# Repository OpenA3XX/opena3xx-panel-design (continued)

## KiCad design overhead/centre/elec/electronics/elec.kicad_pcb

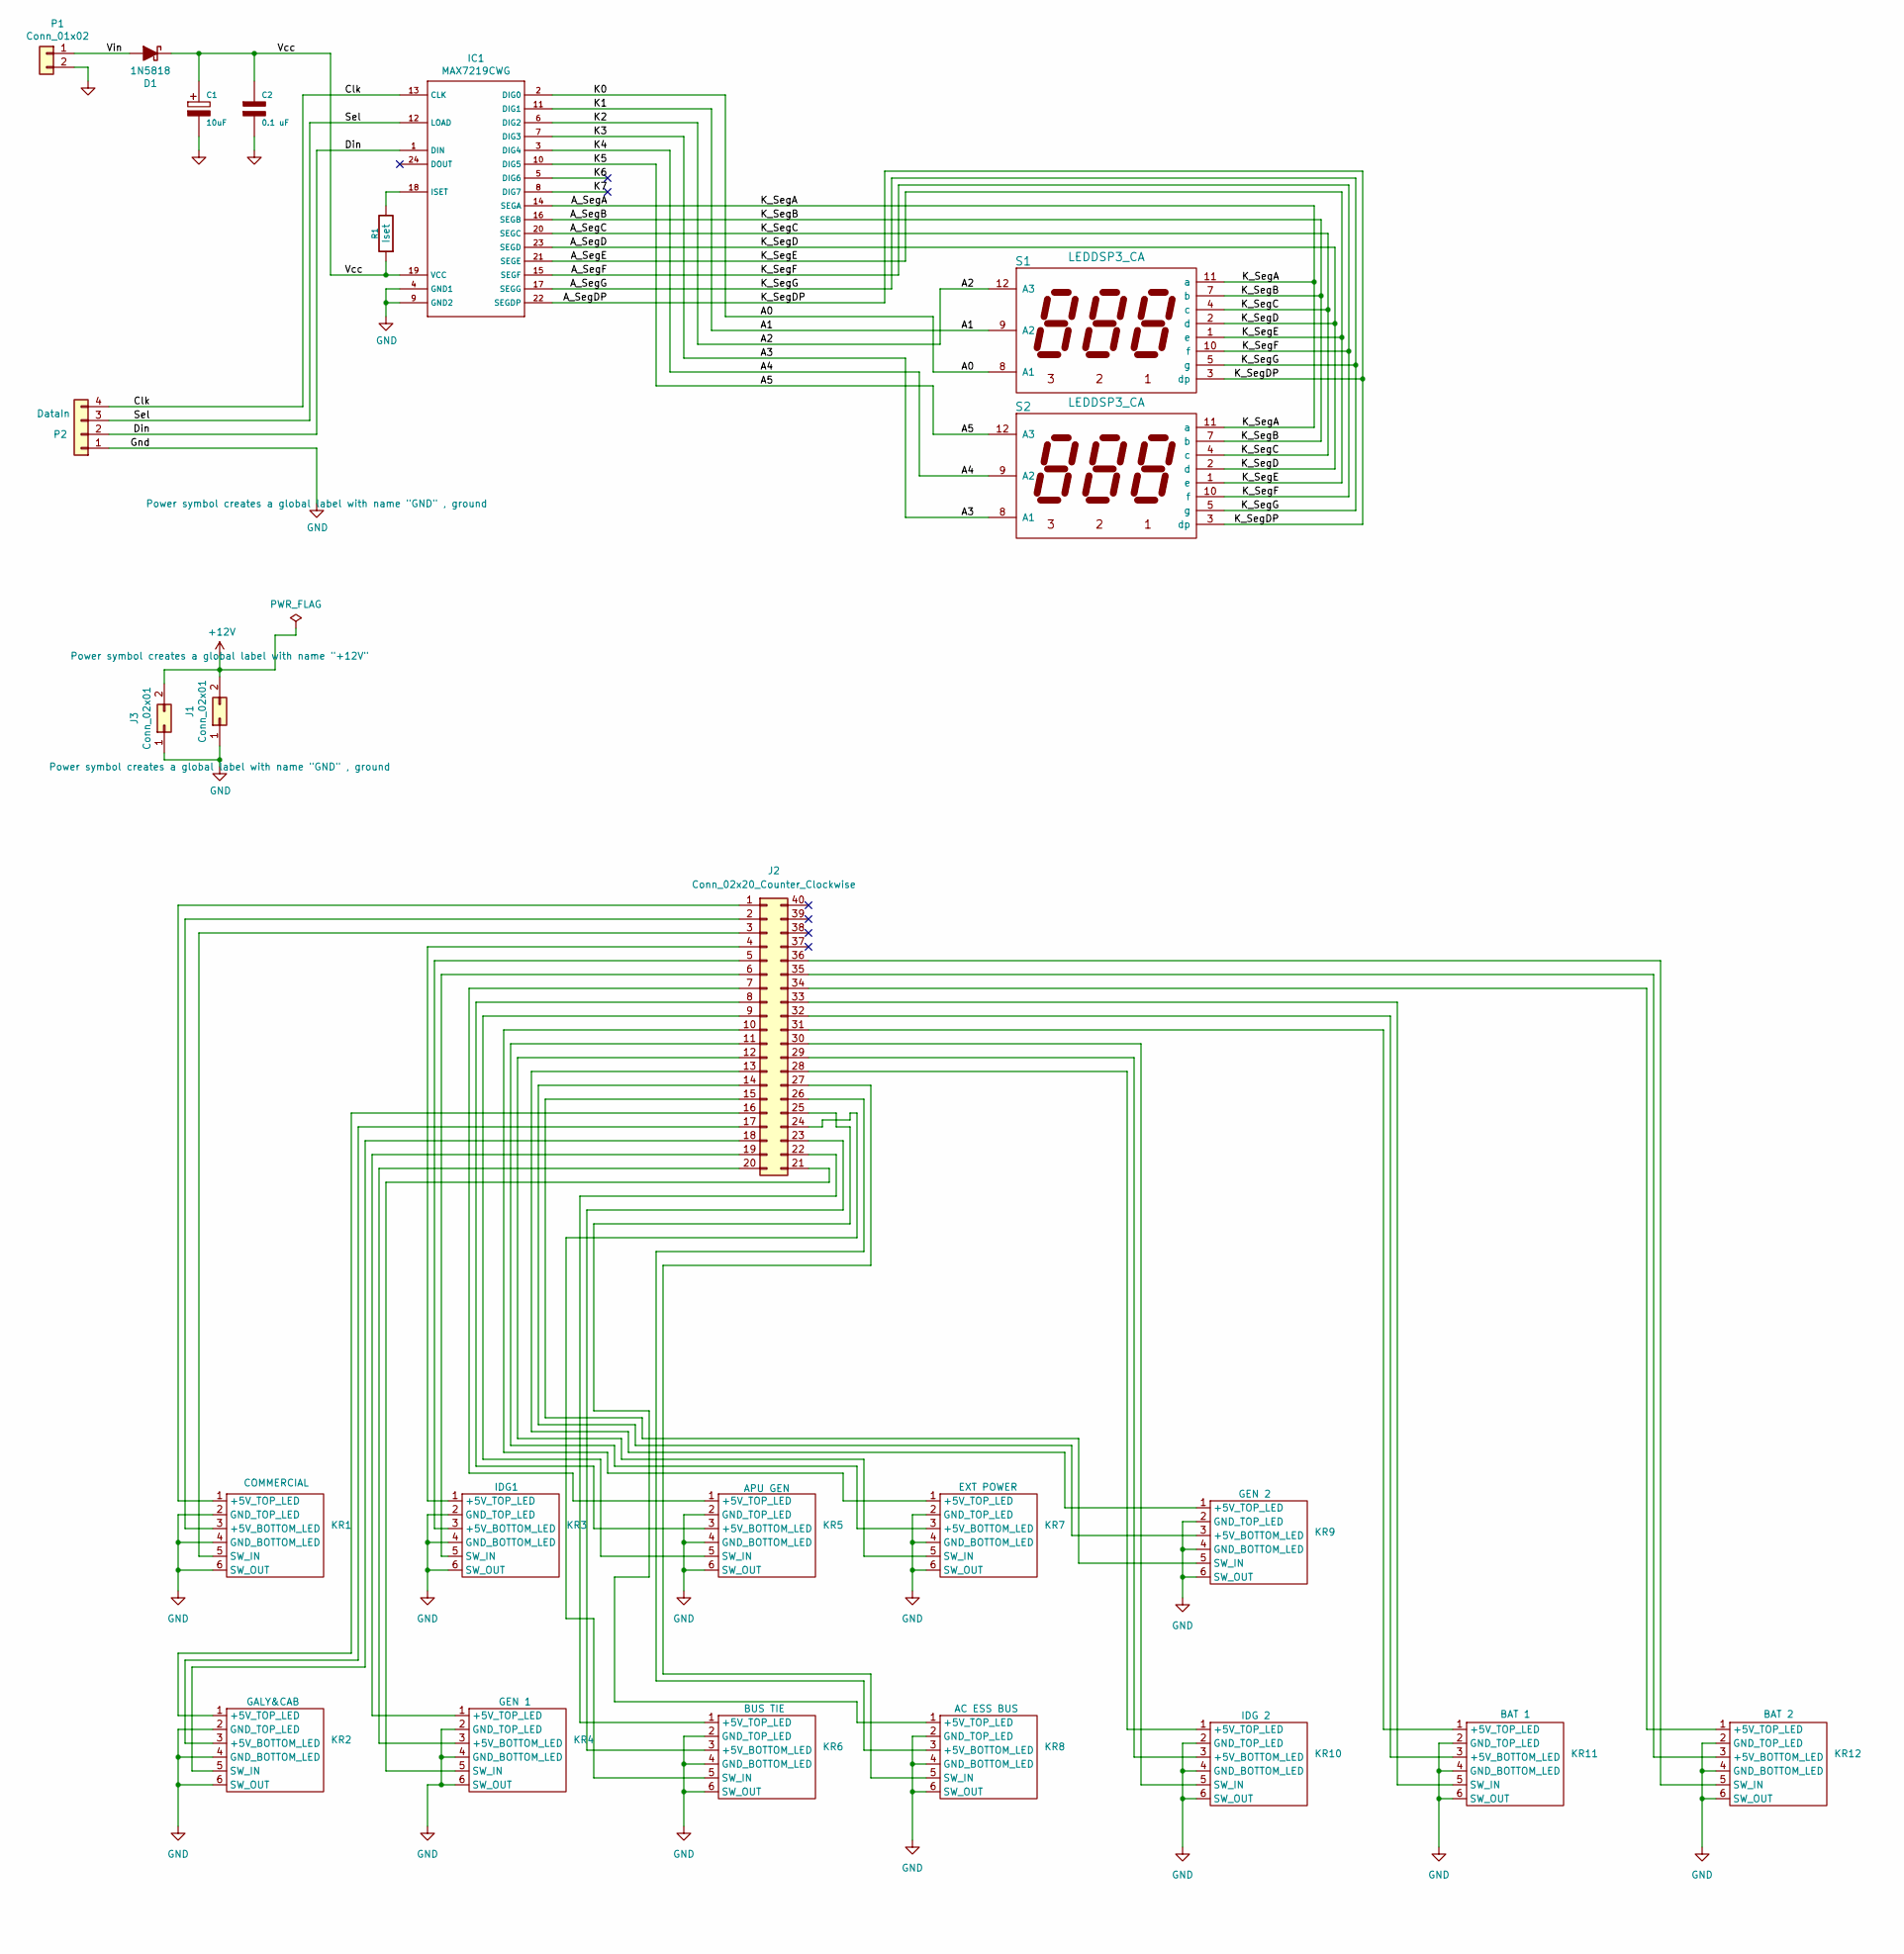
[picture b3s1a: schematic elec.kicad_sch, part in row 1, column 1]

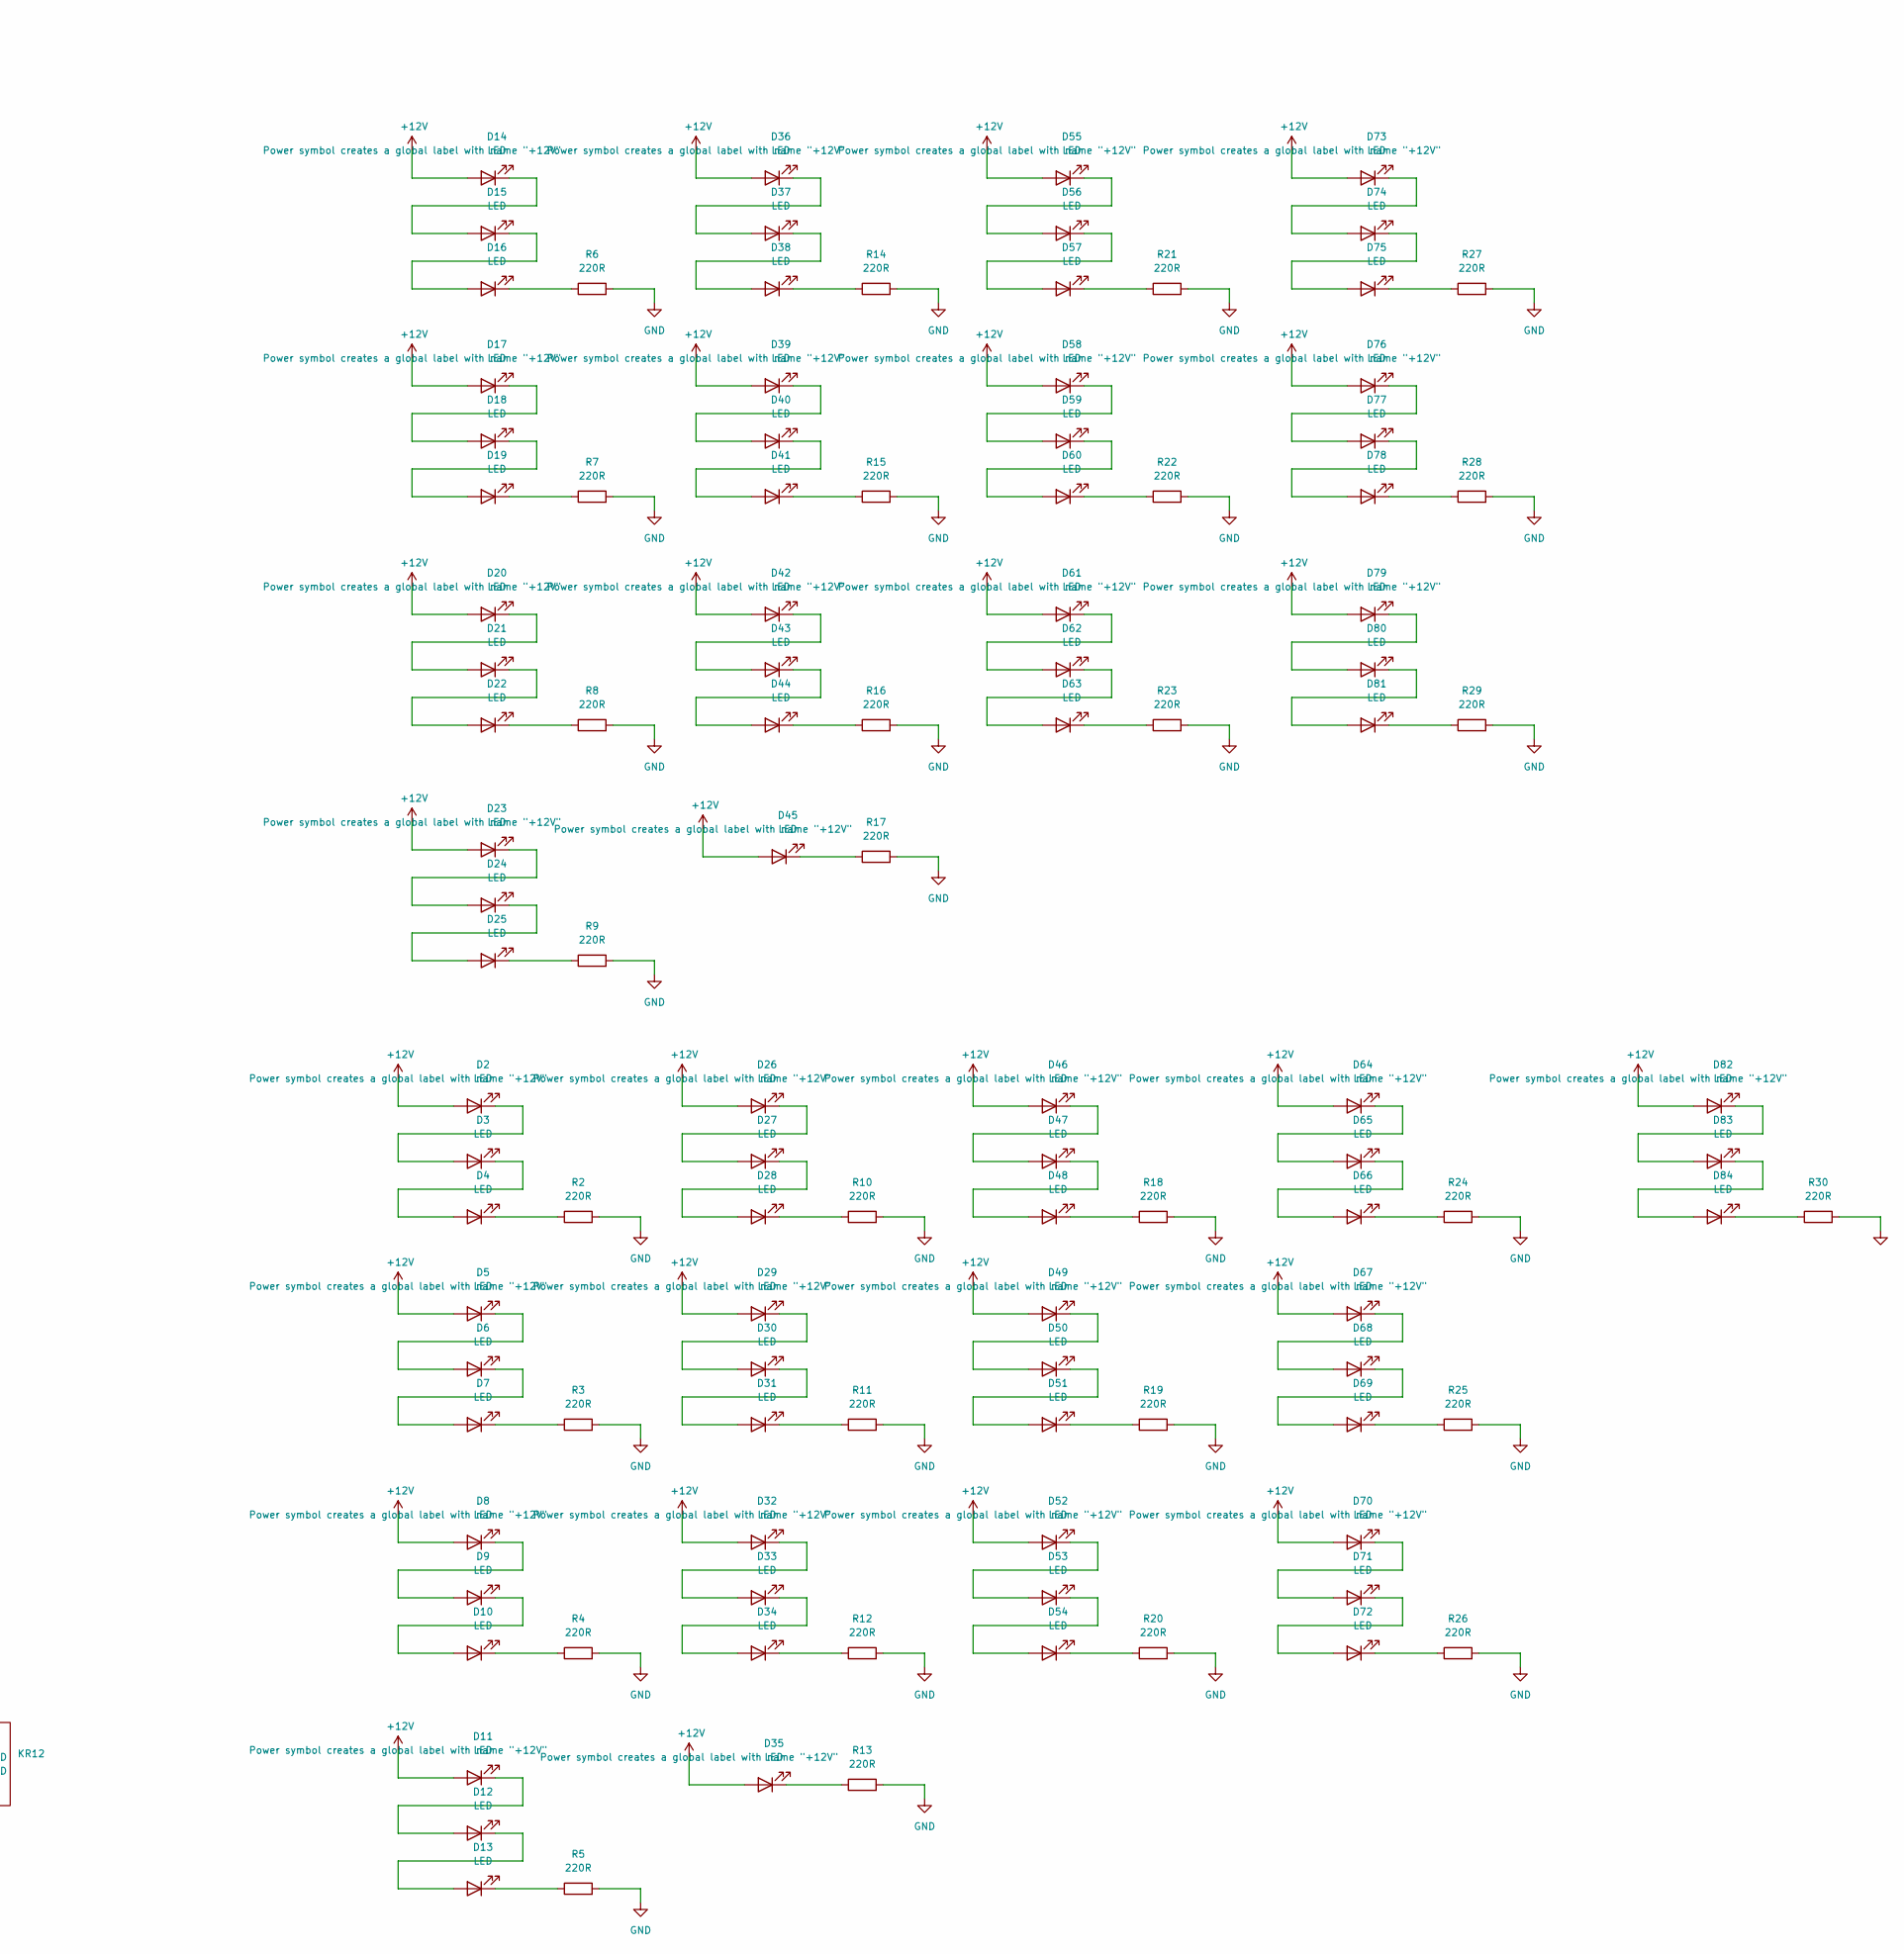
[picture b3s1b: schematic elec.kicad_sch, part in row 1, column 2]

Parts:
C1: 10uF; CP_Radial_D5.0mm_P2.50mm
C2: 0.1 uF; C_1206_3216Metric_Pad1.33x1.80mm_HandSolder
D1: 1N5818; D_SMA_Handsoldering
D2, D3, D4, D5, D6, D7, D8, D9, D10, D11, D12, D13, D14, D15, D16, D17, D18, D19, D20, D21, D22, D23, D24, D25, D26, D27, D28, D29, D30, D31, D32, D33, D34, D35, D36, D37, D38, D39, D40, D41, D42, D43, D44, D45, D46, D47, D48, D49, D50, D51, D52, D53, D54, D55, D56, D57, D58, D59, D60, D61, D62, D63, D64, D65, D66, D67, D68, D69, D70, D71, D72, D73, D74, D75, D76, D77, D78, D79, D80, D81, D82, D83, D84: LED; LED_Everlight-SMD3528_3.5x2.8mm_67-21ST
IC1: MAX7219CWG; SOIC-24W_7.5x15.4mm_P1.27mm
J1, J3: Conn_02x01; TerminalBlock_bornier-2_P5.08mm
J2: Conn_02x20_Counter_Clockwise; PinHeader_2x20_P2.54mm_Vertical
KR1, KR2, KR3, KR4, KR5, KR6, KR7, KR8, KR9, KR10, KR11, KR12: Korry Switch
P1: Conn_01x02; TerminalBlock_bornier-2_P5.08mm
P2: DataIn; PinHeader_1x04_P2.54mm_Vertical
R1: Iset; R_Axial_DIN0207_L6.3mm_D2.5mm_P10.16mm_Horizontal
R2, R3, R4, R5, R6, R7, R8, R9, R10, R11, R12, R13, R14, R15, R16, R17, R18, R19, R20, R21, R22, R23, R24, R25, R26, R27, R28, R29, R30: 220R; R_1206_3216Metric_Pad1.30x1.75mm_HandSolder
S1, S2: LEDDSP3_CA; Disp7s3x_036

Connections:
+12V: D2.2 (A), D5.2 (A), D8.2 (A), D11.2 (A), D14.2 (A), D17.2 (A), D20.2 (A), D23.2 (A), D26.2 (A), D29.2 (A), D32.2 (A), D35.2 (A), D36.2 (A), D39.2 (A), D42.2 (A), D45.2 (A), D46.2 (A), D49.2 (A), D52.2 (A), D55.2 (A), D58.2 (A), D61.2 (A), D64.2 (A), D67.2 (A), D70.2 (A), D73.2 (A), D76.2 (A), D79.2 (A), D82.2 (A), J1.2, J3.2
/A0: IC1.2 (DIG0), S1.8 (A1)
/A1: IC1.11 (DIG1), S1.9 (A2)
/A2: IC1.6 (DIG2), S1.12 (A3)
/A3: IC1.7 (DIG3), S2.8 (A1)
/A4: IC1.3 (DIG4), S2.9 (A2)
/A5: IC1.10 (DIG5), S2.12 (A3)
/A_SegA: IC1.14 (SEGA), S1.11 (a), S2.11 (a)
/A_SegB: IC1.16 (SEGB), S1.7 (b), S2.7 (b)
/A_SegC: IC1.20 (SEGC), S1.4 (c), S2.4 (c)
/A_SegD: IC1.23 (SEGD), S1.2 (d), S2.2 (d)
/A_SegDP: IC1.22 (SEGDP), S1.3 (dp), S2.3 (dp)
/A_SegE: IC1.21 (SEGE), S1.1 (e), S2.1 (e)
/A_SegF: IC1.15 (SEGF), S1.10 (f), S2.10 (f)
/A_SegG: IC1.17 (SEGG), S1.5 (g), S2.5 (g)
/Clk: IC1.13 (CLK), P2.4
/Din: IC1.1 (DIN), P2.2
/K6: IC1.5 (DIG6)
/K7: IC1.8 (DIG7)
/Sel: IC1.12 (LOAD), P2.3
/Vcc: C1.1, C2.1, D1.1 (K), IC1.19 (VCC), R1.1
/Vin: D1.2 (A), P1.1
GND: C1.2, C2.2, IC1.4 (GND1), IC1.9 (GND2), J1.1, J3.1, KR1.2 (GND_TOP_LED), KR1.4 (GND_BOTTOM_LED), KR1.6 (SW_OUT), KR2.2 (GND_TOP_LED), KR2.4 (GND_BOTTOM_LED), KR2.6 (SW_OUT), KR3.2 (GND_TOP_LED), KR3.4 (GND_BOTTOM_LED), KR3.6 (SW_OUT), KR4.2 (GND_TOP_LED), KR4.4 (GND_BOTTOM_LED), KR4.6 (SW_OUT), KR5.2 (GND_TOP_LED), KR5.4 (GND_BOTTOM_LED), KR5.6 (SW_OUT), KR6.2 (GND_TOP_LED), KR6.4 (GND_BOTTOM_LED), KR6.6 (SW_OUT), KR7.2 (GND_TOP_LED), KR7.4 (GND_BOTTOM_LED), KR7.6 (SW_OUT), KR8.2 (GND_TOP_LED), KR8.4 (GND_BOTTOM_LED), KR8.6 (SW_OUT), KR9.2 (GND_TOP_LED), KR9.4 (GND_BOTTOM_LED), KR9.6 (SW_OUT), KR10.2 (GND_TOP_LED), KR10.4 (GND_BOTTOM_LED), KR10.6 (SW_OUT), KR11.2 (GND_TOP_LED), KR11.4 (GND_BOTTOM_LED), KR11.6 (SW_OUT), KR12.2 (GND_TOP_LED), KR12.4 (GND_BOTTOM_LED), KR12.6 (SW_OUT), P1.2, P2.1, R2.2, R3.2, R4.2, R5.2, R6.2, R7.2, R8.2, R9.2, R10.2, R11.2, R12.2, R13.2, R14.2, R15.2, R16.2, R17.2, R18.2, R19.2, R20.2, R21.2, R22.2, R23.2, R24.2, R25.2, R26.2, R27.2, R28.2, R29.2, R30.2
unnamed: D2.1 (K), D3.2 (A)
unnamed: D3.1 (K), D4.2 (A)
unnamed: D4.1 (K), R2.1
unnamed: D5.1 (K), D6.2 (A)
unnamed: D6.1 (K), D7.2 (A)
unnamed: D7.1 (K), R3.1
unnamed: D8.1 (K), D9.2 (A)
unnamed: D9.1 (K), D10.2 (A)
unnamed: D10.1 (K), R4.1
unnamed: D11.1 (K), D12.2 (A)
unnamed: D12.1 (K), D13.2 (A)
unnamed: D13.1 (K), R5.1
unnamed: D14.1 (K), D15.2 (A)
unnamed: D15.1 (K), D16.2 (A)
unnamed: D16.1 (K), R6.1
unnamed: D17.1 (K), D18.2 (A)
unnamed: D18.1 (K), D19.2 (A)
unnamed: D19.1 (K), R7.1
unnamed: D20.1 (K), D21.2 (A)
unnamed: D21.1 (K), D22.2 (A)
unnamed: D22.1 (K), R8.1
unnamed: D23.1 (K), D24.2 (A)
unnamed: D24.1 (K), D25.2 (A)
unnamed: D25.1 (K), R9.1
unnamed: D26.1 (K), D27.2 (A)
unnamed: D27.1 (K), D28.2 (A)
unnamed: D28.1 (K), R10.1
unnamed: D29.1 (K), D30.2 (A)
unnamed: D30.1 (K), D31.2 (A)
unnamed: D31.1 (K), R11.1
unnamed: D32.1 (K), D33.2 (A)
unnamed: D33.1 (K), D34.2 (A)
unnamed: D34.1 (K), R12.1
unnamed: D35.1 (K), R13.1
unnamed: D36.1 (K), D37.2 (A)
unnamed: D37.1 (K), D38.2 (A)
unnamed: D38.1 (K), R14.1
unnamed: D39.1 (K), D40.2 (A)
unnamed: D40.1 (K), D41.2 (A)
unnamed: D41.1 (K), R15.1
unnamed: D42.1 (K), D43.2 (A)
unnamed: D43.1 (K), D44.2 (A)
unnamed: D44.1 (K), R16.1
unnamed: D45.1 (K), R17.1
unnamed: D46.1 (K), D47.2 (A)
unnamed: D47.1 (K), D48.2 (A)
unnamed: D48.1 (K), R18.1
unnamed: D49.1 (K), D50.2 (A)
unnamed: D50.1 (K), D51.2 (A)
unnamed: D51.1 (K), R19.1
unnamed: D52.1 (K), D53.2 (A)
unnamed: D53.1 (K), D54.2 (A)
unnamed: D54.1 (K), R20.1
unnamed: D55.1 (K), D56.2 (A)
unnamed: D56.1 (K), D57.2 (A)
unnamed: D57.1 (K), R21.1
unnamed: D58.1 (K), D59.2 (A)
unnamed: D59.1 (K), D60.2 (A)
unnamed: D60.1 (K), R22.1
unnamed: D61.1 (K), D62.2 (A)
unnamed: D62.1 (K), D63.2 (A)
unnamed: D63.1 (K), R23.1
unnamed: D64.1 (K), D65.2 (A)
unnamed: D65.1 (K), D66.2 (A)
unnamed: D66.1 (K), R24.1
unnamed: D67.1 (K), D68.2 (A)
unnamed: D68.1 (K), D69.2 (A)
unnamed: D69.1 (K), R25.1
unnamed: D70.1 (K), D71.2 (A)
unnamed: D71.1 (K), D72.2 (A)
unnamed: D72.1 (K), R26.1
unnamed: D73.1 (K), D74.2 (A)
unnamed: D74.1 (K), D75.2 (A)
unnamed: D75.1 (K), R27.1
unnamed: D76.1 (K), D77.2 (A)
unnamed: D77.1 (K), D78.2 (A)
unnamed: D78.1 (K), R28.1
unnamed: D79.1 (K), D80.2 (A)
unnamed: D80.1 (K), D81.2 (A)
unnamed: D81.1 (K), R29.1
unnamed: D82.1 (K), D83.2 (A)
unnamed: D83.1 (K), D84.2 (A)
unnamed: D84.1 (K), R30.1
unnamed: IC1.18 (ISET), R1.2
unnamed: J2.1, KR1.1 (+5V_TOP_LED)
unnamed: J2.2, KR1.3 (+5V_BOTTOM_LED)
unnamed: J2.3, KR1.5 (SW_IN)
unnamed: J2.4, KR3.1 (+5V_TOP_LED)
unnamed: J2.5, KR3.3 (+5V_BOTTOM_LED)
unnamed: J2.6, KR3.5 (SW_IN)
unnamed: J2.7, KR5.1 (+5V_TOP_LED)
unnamed: J2.8, KR5.3 (+5V_BOTTOM_LED)
unnamed: J2.9, KR5.5 (SW_IN)
unnamed: J2.10, KR7.1 (+5V_TOP_LED)
unnamed: J2.11, KR7.3 (+5V_BOTTOM_LED)
unnamed: J2.12, KR7.5 (SW_IN)
unnamed: J2.13, KR9.1 (+5V_TOP_LED)
unnamed: J2.14, KR9.3 (+5V_BOTTOM_LED)
unnamed: J2.15, KR9.5 (SW_IN)
unnamed: J2.16, KR2.1 (+5V_TOP_LED)
unnamed: J2.17, KR2.3 (+5V_BOTTOM_LED)
unnamed: J2.18, KR2.5 (SW_IN)
unnamed: J2.19, KR4.1 (+5V_TOP_LED)
unnamed: J2.20, KR4.3 (+5V_BOTTOM_LED)
unnamed: J2.21, KR4.5 (SW_IN)
unnamed: J2.22, KR6.1 (+5V_TOP_LED)
unnamed: J2.23, KR6.3 (+5V_BOTTOM_LED)
unnamed: J2.26, KR8.3 (+5V_BOTTOM_LED)
unnamed: J2.27, KR8.5 (SW_IN)
unnamed: J2.28, KR10.1 (+5V_TOP_LED)
unnamed: J2.29, KR10.3 (+5V_BOTTOM_LED)
unnamed: J2.30, KR10.5 (SW_IN)
unnamed: J2.31, KR11.1 (+5V_TOP_LED)
unnamed: J2.32, KR11.3 (+5V_BOTTOM_LED)
unnamed: J2.33, KR11.5 (SW_IN)
unnamed: J2.34, KR12.1 (+5V_TOP_LED)
unnamed: J2.35, KR12.3 (+5V_BOTTOM_LED)
unnamed: J2.36, KR12.5 (SW_IN)

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
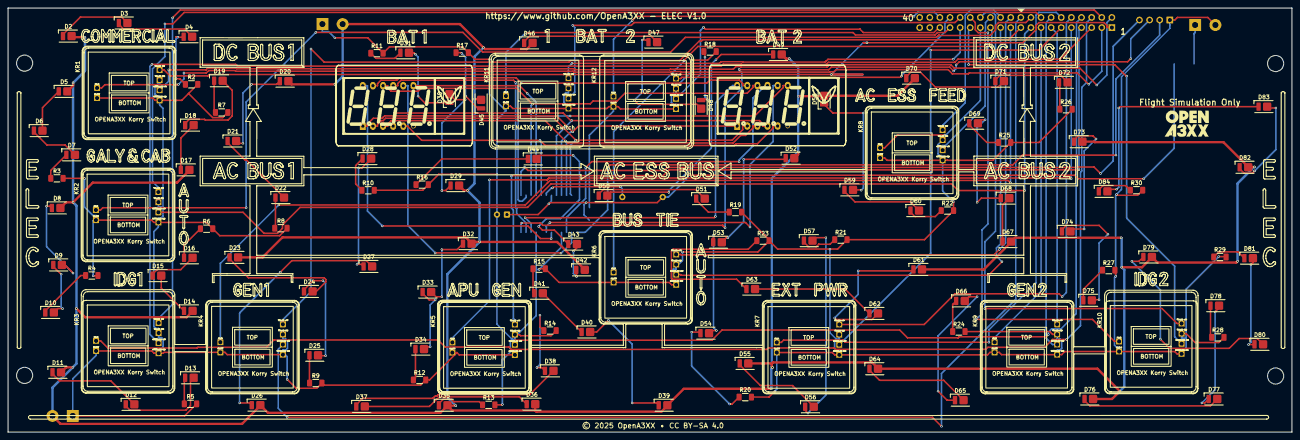
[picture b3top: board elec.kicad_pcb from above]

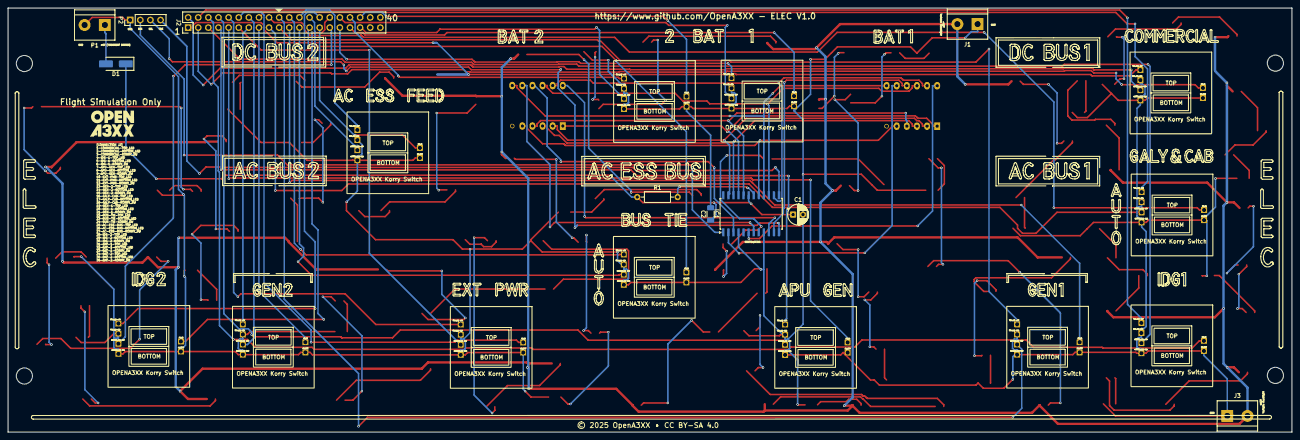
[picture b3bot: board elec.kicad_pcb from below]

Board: 2 copper layers, 322.3 x 106.5 mm, 138 parts (11 on the bottom side), 141 nets.

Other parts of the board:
bottom: LOGO; OpenA3XXLogoSmall
top: LOGO; OpenA3XXLogoSmall

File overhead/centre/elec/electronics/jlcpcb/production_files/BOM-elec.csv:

Comment,Designator,Footprint,LCSC,Quantity
LED,"D10,D11,D12,D13,D14,D15,D16,D17,D18,D19,D2,D20,D21,D22,D23,D24,D25,D26,D27,D28,D29,D3,D30,D31,D32,D33,D34,D35,D36,D37,D38,D39,D4,D40,D41,D42,D43,D44,D45,D46,D47,D48,D49,D5,D50,D51,D52,D53,D54,D55,D56,D57,D58,D59,D6,D60,D61,D62,D63,D64,D65,D66,D67,D68,D69,D7,D70,D71,D72,D73,D74,D75,D76,D77,D78,D79,D8,D80,D81,D82,D83,D84,D9",LED_Everlight-SMD3528_3.5x2.8mm_67-21ST,C2843803,83
220R,"R10,R11,R12,R13,R14,R15,R16,R17,R18,R19,R2,R20,R21,R22,R23,R24,R25,R26,R27,R28,R29,R3,R30,R4,R5,R6,R7,R8,R9",R_1206_3216Metric_Pad1.30x1.75mm_HandSolder,C2933785,29
10uF,C1,CP_Radial_D5.0mm_P2.50mm,C32856,1
Conn_02x01,"J1,J3",TerminalBlock_bornier-2_P5.08mm,C3703,2
1N5818,D1,D_SMA_Handsoldering,C437955,1
DataIn,P2,PinHeader_1x04_P2.54mm_Vertical,C5116483,1
Conn_01x02,P1,TerminalBlock_bornier-2_P5.08mm,C592976,1
Conn_02x20_Counter_Clockwise,J2,PinHeader_2x20_P2.54mm_Vertical,C725892,1
0.1 uF,C2,C_1206_3216Metric_Pad1.33x1.80mm_HandSolder,C7432784,1
MAX7219CWG,IC1,SOIC-24W_7.5x15.4mm_P1.27mm,C9964,1
~,KR8,Korry Switch,,1
~,KR3,Korry Switch,,1
~,KR11,Korry Switch,,1
~,KR7,Korry Switch,,1
~,KR1,Korry Switch,,1
~,KR9,Korry Switch,,1
~,KR10,Korry Switch,,1
LEDDSP3_CA,S1,Disp7s3x_036,,1
~,KR5,Korry Switch,,1
~,KR12,Korry Switch,,1
~,KR2,Korry Switch,,1
LEDDSP3_CA,S2,Disp7s3x_036,,1
~,KR4,Korry Switch,,1
~,KR6,Korry Switch,,1
Iset,R1,R_Axial_DIN0207_L6.3mm_D2.5mm_P10.16mm_Horizontal,,1

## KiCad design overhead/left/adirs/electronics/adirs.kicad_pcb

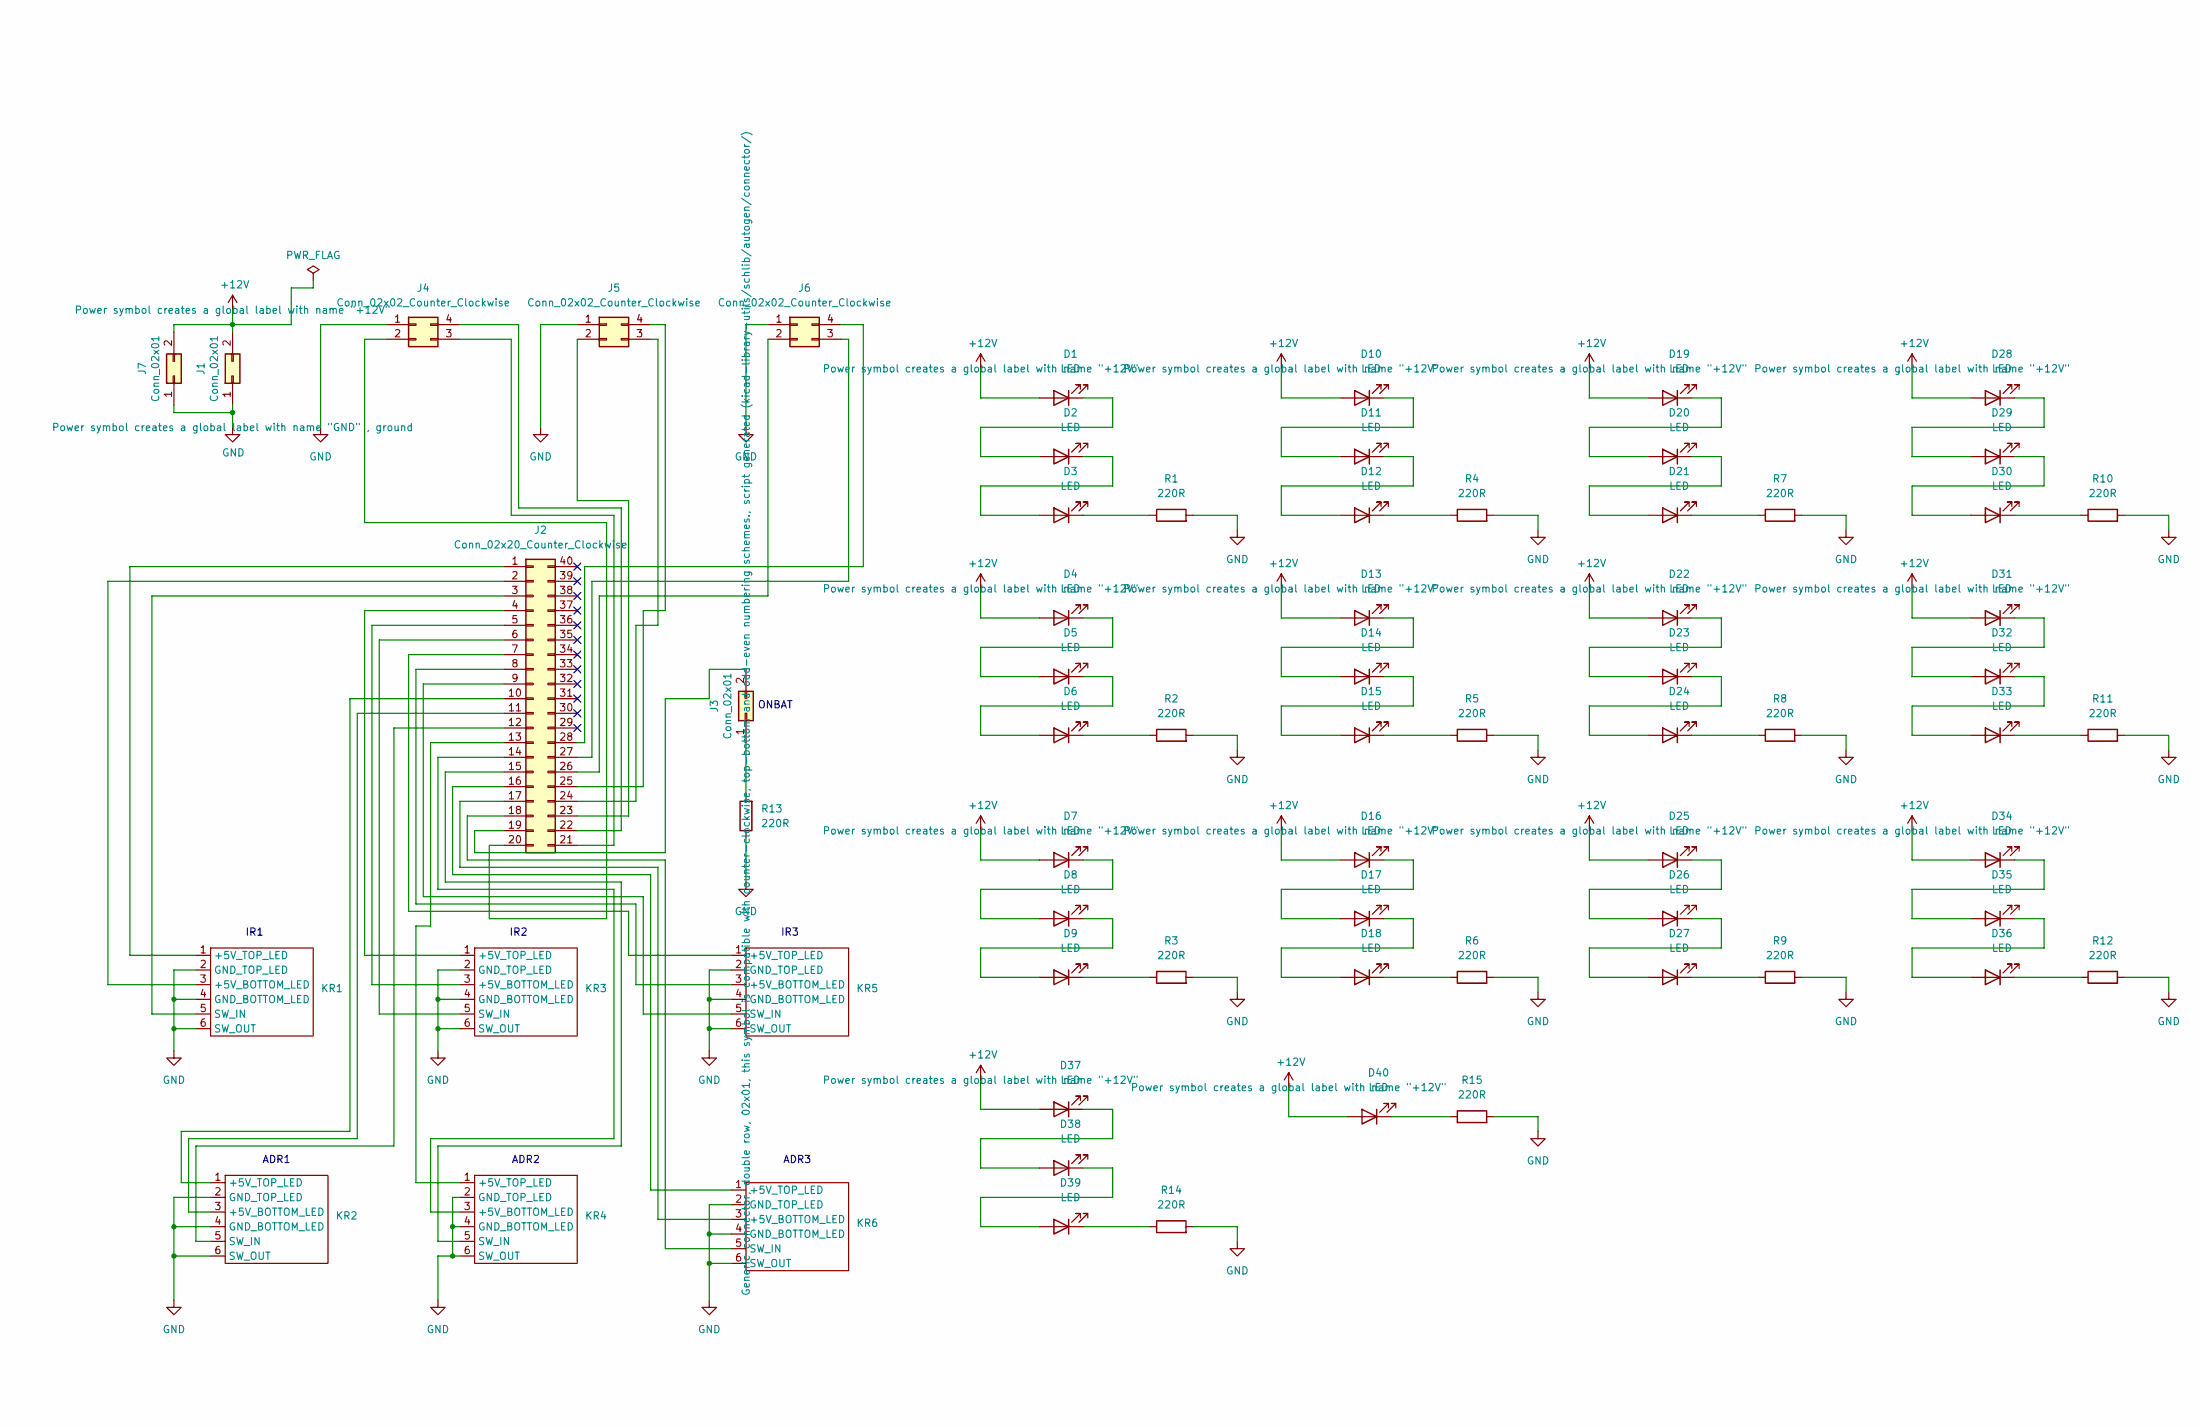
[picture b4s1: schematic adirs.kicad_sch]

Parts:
D1, D2, D3, D4, D5, D6, D7, D8, D9, D10, D11, D12, D13, D14, D15, D16, D17, D18, D19, D20, D21, D22, D23, D24, D25, D26, D27, D28, D29, D30, D31, D32, D33, D34, D35, D36, D37, D38, D39, D40: LED; LED_Everlight-SMD3528_3.5x2.8mm_67-21ST
J1, J7: Conn_02x01; TerminalBlock_bornier-2_P5.08mm
J2: Conn_02x20_Counter_Clockwise; PinHeader_2x20_P2.54mm_Vertical
J3: Conn_02x01; PinHeader_1x02_P2.54mm_Vertical
J4, J5, J6: Conn_02x02_Counter_Clockwise; PinHeader_1x04_P2.54mm_Vertical
KR1, KR2, KR3, KR4, KR5, KR6: Korry Switch
R1, R2, R3, R4, R5, R6, R7, R8, R9, R10, R11, R12, R13, R14, R15: 220R; R_1206_3216Metric_Pad1.30x1.75mm_HandSolder

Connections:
+12V: D1.2 (A), D4.2 (A), D7.2 (A), D10.2 (A), D13.2 (A), D16.2 (A), D19.2 (A), D22.2 (A), D25.2 (A), D28.2 (A), D31.2 (A), D34.2 (A), D37.2 (A), D40.2 (A), J1.2, J7.2
GND: J1.1, J4.1, J5.1, J6.1, J7.1, KR1.2 (GND_TOP_LED), KR1.4 (GND_BOTTOM_LED), KR1.6 (SW_OUT), KR2.2 (GND_TOP_LED), KR2.4 (GND_BOTTOM_LED), KR2.6 (SW_OUT), KR3.2 (GND_TOP_LED), KR3.4 (GND_BOTTOM_LED), KR3.6 (SW_OUT), KR4.2 (GND_TOP_LED), KR4.4 (GND_BOTTOM_LED), KR4.6 (SW_OUT), KR5.2 (GND_TOP_LED), KR5.4 (GND_BOTTOM_LED), KR5.6 (SW_OUT), KR6.2 (GND_TOP_LED), KR6.4 (GND_BOTTOM_LED), KR6.6 (SW_OUT), R1.2, R2.2, R3.2, R4.2, R5.2, R6.2, R7.2, R8.2, R9.2, R10.2, R11.2, R12.2, R13.1, R14.2, R15.2
unnamed: D1.1 (K), D2.2 (A)
unnamed: D2.1 (K), D3.2 (A)
unnamed: D3.1 (K), R1.1
unnamed: D4.1 (K), D5.2 (A)
unnamed: D5.1 (K), D6.2 (A)
unnamed: D6.1 (K), R2.1
unnamed: D7.1 (K), D8.2 (A)
unnamed: D8.1 (K), D9.2 (A)
unnamed: D9.1 (K), R3.1
unnamed: D10.1 (K), D11.2 (A)
unnamed: D11.1 (K), D12.2 (A)
unnamed: D12.1 (K), R4.1
unnamed: D13.1 (K), D14.2 (A)
unnamed: D14.1 (K), D15.2 (A)
unnamed: D15.1 (K), R5.1
unnamed: D16.1 (K), D17.2 (A)
unnamed: D17.1 (K), D18.2 (A)
unnamed: D18.1 (K), R6.1
unnamed: D19.1 (K), D20.2 (A)
unnamed: D20.1 (K), D21.2 (A)
unnamed: D21.1 (K), R7.1
unnamed: D22.1 (K), D23.2 (A)
unnamed: D23.1 (K), D24.2 (A)
unnamed: D24.1 (K), R8.1
unnamed: D25.1 (K), D26.2 (A)
unnamed: D26.1 (K), D27.2 (A)
unnamed: D27.1 (K), R9.1
unnamed: D28.1 (K), D29.2 (A)
unnamed: D29.1 (K), D30.2 (A)
unnamed: D30.1 (K), R10.1
unnamed: D31.1 (K), D32.2 (A)
unnamed: D32.1 (K), D33.2 (A)
unnamed: D33.1 (K), R11.1
unnamed: D34.1 (K), D35.2 (A)
unnamed: D35.1 (K), D36.2 (A)
unnamed: D36.1 (K), R12.1
unnamed: D37.1 (K), D38.2 (A)
unnamed: D38.1 (K), D39.2 (A)
unnamed: D39.1 (K), R14.1
unnamed: D40.1 (K), R15.1
unnamed: J2.1, KR1.1 (+5V_TOP_LED)
unnamed: J2.2, KR1.3 (+5V_BOTTOM_LED)
unnamed: J2.3, KR1.5 (SW_IN)
unnamed: J2.4, KR3.1 (+5V_TOP_LED)
unnamed: J2.5, KR3.3 (+5V_BOTTOM_LED)
unnamed: J2.6, KR3.5 (SW_IN)
unnamed: J2.7, KR5.1 (+5V_TOP_LED)
unnamed: J2.8, KR5.3 (+5V_BOTTOM_LED)
unnamed: J2.9, KR5.5 (SW_IN)
unnamed: J2.10, KR2.1 (+5V_TOP_LED)
unnamed: J2.11, KR2.3 (+5V_BOTTOM_LED)
unnamed: J2.12, KR2.5 (SW_IN)
unnamed: J2.13, KR4.1 (+5V_TOP_LED)
unnamed: J2.14, KR4.3 (+5V_BOTTOM_LED)
unnamed: J2.15, KR4.5 (SW_IN)
unnamed: J2.16, KR6.1 (+5V_TOP_LED)
unnamed: J2.17, KR6.3 (+5V_BOTTOM_LED)
unnamed: J2.18, KR6.5 (SW_IN)
unnamed: J2.19, J3.2
unnamed: J2.20, J4.2
unnamed: J2.21, J4.3
unnamed: J2.22, J4.4
unnamed: J2.23, J5.2
unnamed: J2.24, J5.3
unnamed: J2.25, J5.4
unnamed: J2.26, J6.2
unnamed: J2.27, J6.3
unnamed: J2.28, J6.4
unnamed: J3.1, R13.2

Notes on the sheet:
IR1
IR2
ONBAT
IR3
ADR2
ADR3
ADR1

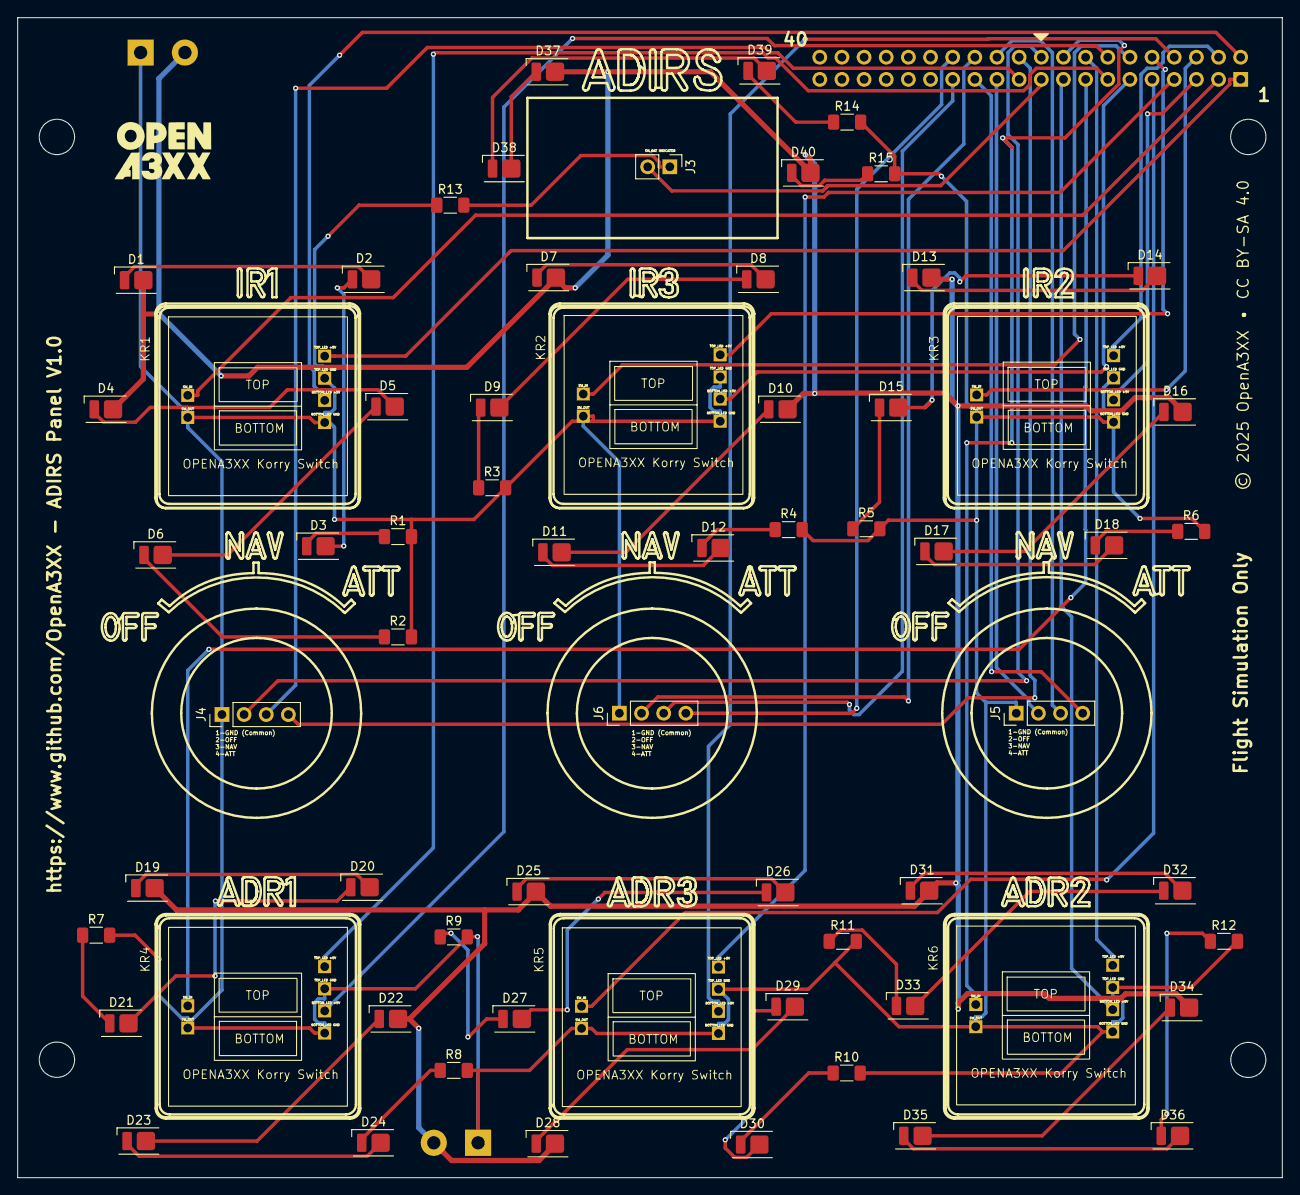
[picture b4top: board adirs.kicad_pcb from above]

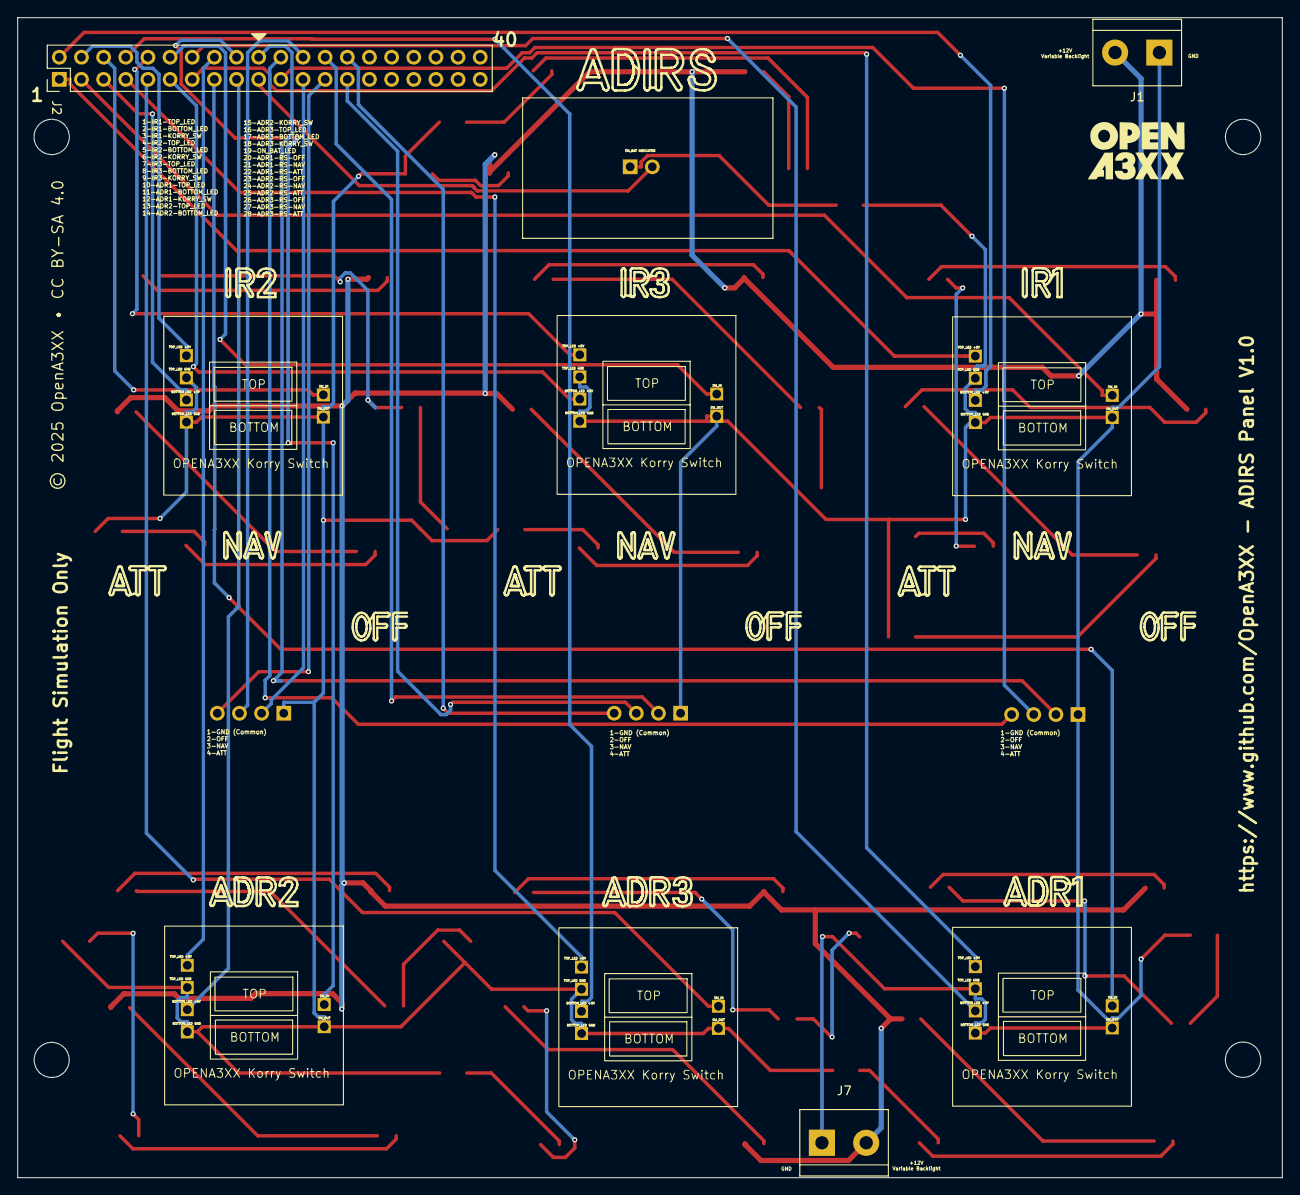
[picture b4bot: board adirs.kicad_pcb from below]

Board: 2 copper layers, 145.0 x 133.0 mm, 69 parts (4 on the bottom side), 71 nets.

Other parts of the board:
Bottom: LOGO; OpenA3XXLogoSmall

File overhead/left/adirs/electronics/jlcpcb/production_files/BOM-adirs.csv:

Comment,Designator,Footprint,LCSC,Quantity
LED,"D1,D10,D11,D12,D13,D14,D15,D16,D17,D18,D19,D2,D20,D21,D22,D23,D24,D25,D26,D27,D28,D29,D3,D30,D31,D32,D33,D34,D35,D36,D37,D38,D39,D4,D40,D5,D6,D7,D8,D9",LED_Everlight-SMD3528_3.5x2.8mm_67-21ST,C2843803,40
Conn_02x01,J3,PinHeader_1x02_P2.54mm_Vertical,C2915055,1
220R,"R1,R10,R11,R12,R13,R14,R15,R2,R3,R4,R5,R6,R7,R8,R9",R_1206_3216Metric_Pad1.30x1.75mm_HandSolder,C2933785,15
Conn_02x02_Counter_Clockwise,"J4,J5,J6",PinHeader_1x04_P2.54mm_Vertical,C5116483,3
Conn_02x01,"J1,J7",TerminalBlock_bornier-2_P5.08mm,C592976,2
Conn_02x20_Counter_Clockwise,J2,PinHeader_2x20_P2.54mm_Vertical,C725892,1
~,KR3,Korry Switch,,1
~,KR5,Korry Switch,,1
~,KR6,Korry Switch,,1
~,KR4,Korry Switch,,1
~,KR1,Korry Switch,,1
~,KR2,Korry Switch,,1
